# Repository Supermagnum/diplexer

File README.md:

# diplexer
HF+6M lowpass and 4M highpass

The lowpass filter has: 71.5mhz -42dB. 
Highpass filter 52.5mhz -45dB. 50.5mhz -50db

Highpass Ltspice analysis setup:

Highpass frequency analysis ( insertion loss, insertion phase, and return loss):

Highpass Z-in and Z out analysis:

Lowpass LTspice analysis setup:

Lowpass filter frequency analysis ( insertion loss, insertion phase, and return loss):

Lowpass filter Z-in and Z out:

PCB board screenshot:

I had to draw the 1111 SMD footprint because it wasn't included in the Kicad database.
I hope that I haven't messed up.
Shematic for the diplexer:
https://raw.githubusercontent.com/Supermagnum/diplexer/refs/heads/main/diplexer.pdf

Inductors:
You have to make these yourself!
https://github.com/Supermagnum/diplexer/blob/main/Inductors.pdf

Suitable box:
https://www.hammfg.com/part/1457N1601E

All bolt holes is M3.

Animation of assembled PCB:
https://youtu.be/Ffxkk6wFYqY

PCB boards and assembly:

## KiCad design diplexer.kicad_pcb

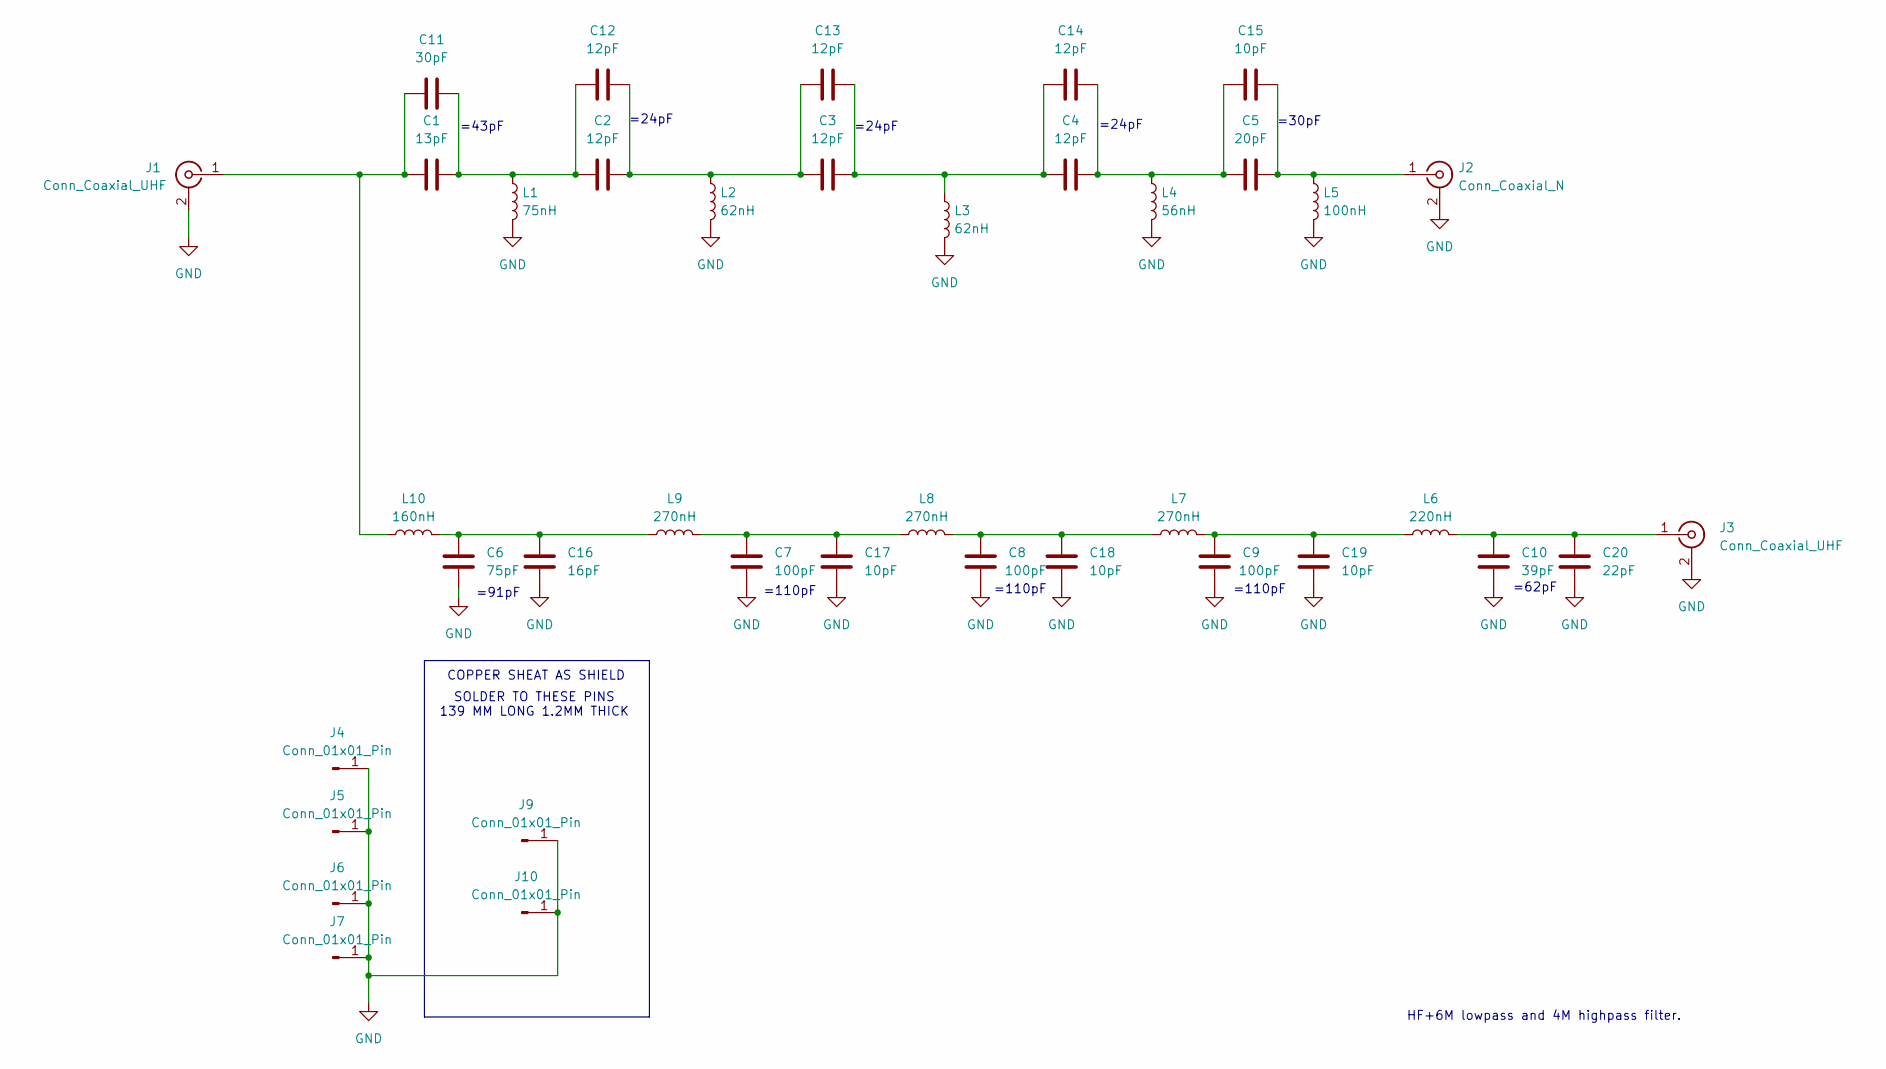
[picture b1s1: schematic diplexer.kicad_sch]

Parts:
C1: 13pF; CAPC2927X178N; MPN VJ1111D130JXGAJ
C2, C3, C4, C12, C13, C14: 12pF; CAPC2927X178N; MPN VJ1111D120GXGQJ
C5: 20pF; CAPC2927X178N; MPN VJ1111D200JXRAJ
C6: 75pF; CAPC2927X178N; MPN VJ1111D750JXGAJ
C7, C8, C9: 100pF; CAPC2927X178N; MPN VJ1111D101GXGQT
C10: 39pF; CAPC2927X178N; MPN VJ1111D390JXRAJ
C11: 30pF; CAPC2927X178N; MPN VJ1111D300GXGQT
C15, C17, C18, C19: 10pF; CAPC2927X178N; MPN VJ1111D100JXRAJ
C16: 16pF; CAPC2927X178N; MPN VJ1111D160GXGQT
C20: 22pF; CAPC2927X178N; MPN VJ1111D220JXRAJ
J1: Conn_Coaxial_UHF; UHF-slant-corr; MPN 083-1R (SO-239)
J2: Conn_Coaxial_N; Conn-N-slant-C; MPN 172117
J3: Conn_Coaxial_UHF; UHF-slant-corr; MPN 83-1R (SO-239)
J4, J5, J6, J7, J9, J10: Conn_01x01_Pin; MountingHole_3.2mm_M3_DIN965_Pad
L1: 75nH; L_Axial_L14.6-hand
L2, L3: 62nH; L_Axial_L14.6-hand
L4: 56nH; L_Axial_L14.6-hand
L5: 100nH; L_Axial_L14.6-hand
L6: 220nH; L_Axial_L14.6-hand
L7, L8, L9: 270nH; L_Axial_L14.6-hand
L10: 160nH; L_Axial_L14.6-hand

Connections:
GND: C6.1, C7.1, C8.1, C9.1, C10.1, C16.2, C17.2, C18.2, C19.2, C20.2, J1.2 (Ext), J1.3, J2.2 (Ext), J2.3, J3.2 (Ext), J3.3, J4.1, J5.1, J6.1, J7.1, J9.1, J10.1, L1.2, L2.2, L3.2, L4.2, L5.2
unnamed: C1.2, C2.1, C11.2, C12.1, L1.1
unnamed: C2.2, C3.1, C12.2, C13.1, L2.1
unnamed: C3.2, C4.1, C13.2, C14.1, L3.1
unnamed: C4.2, C5.1, C14.2, C15.1, L4.1
unnamed: C6.2, C16.1, L9.1, L10.2
unnamed: C7.2, C17.1, L8.1, L9.2
unnamed: C8.2, C18.1, L7.1, L8.2
unnamed: C9.2, C19.1, L6.1, L7.2
unnamed: C1.1, C11.1, J1.1 (In), L10.1
unnamed: C5.2, C15.2, J2.1 (In), L5.1
unnamed: C10.2, C20.1, J3.1 (In), L6.2

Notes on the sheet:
=24pF
=110pF
=43pF
=91pF
=62pF
COPPER SHEAT AS SHIELD
SOLDER TO THESE PINS 139 MM LONG 1.2MM THICK
HF+6M lowpass and 4M highpass filter.
=30pF

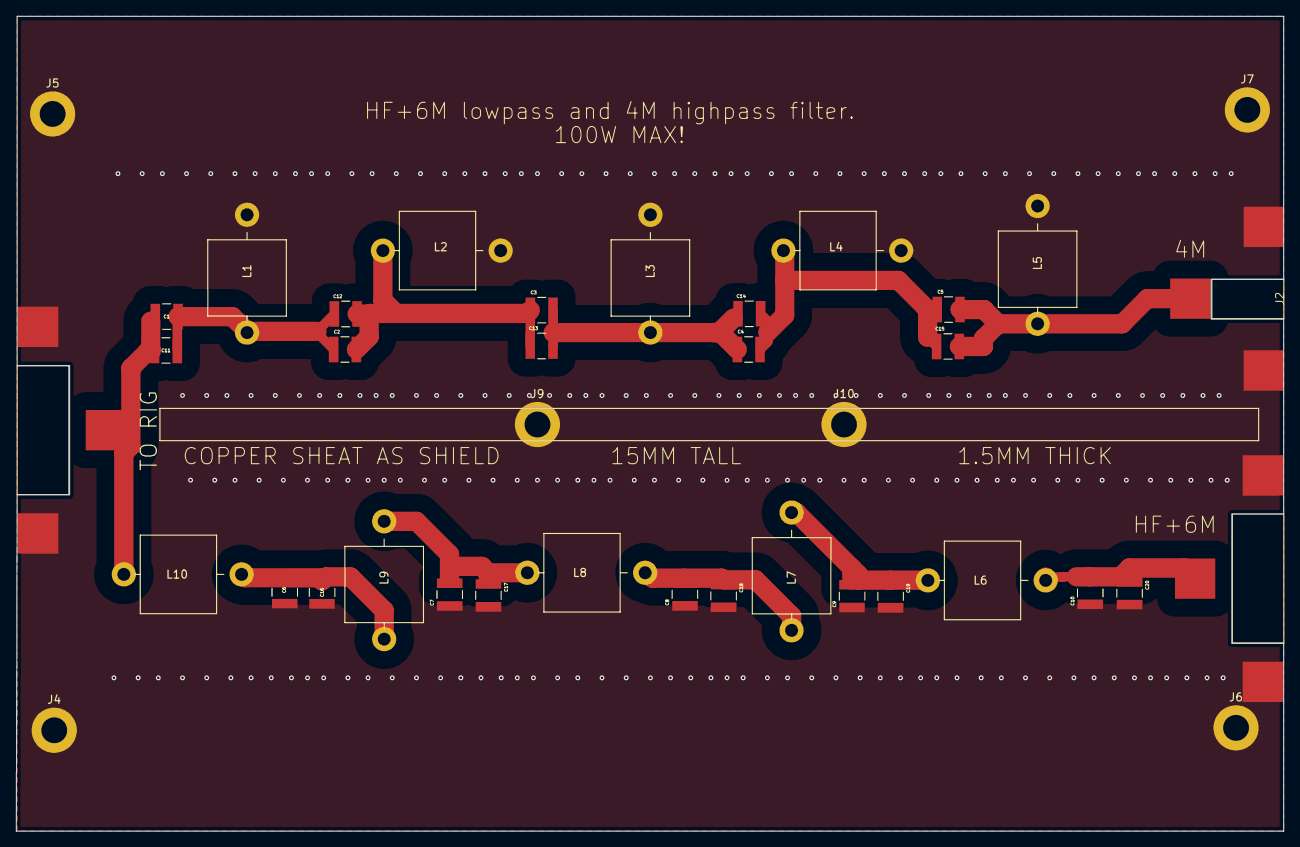
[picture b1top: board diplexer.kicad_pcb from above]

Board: 2 copper layers, 157.1 x 101.0 mm, 39 parts (0 on the bottom side), 12 nets.

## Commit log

2024-03-12 Update README.md
    Added schema diagram
2024-03-12 Inductors
2024-10-11 Add files via upload
    Added gerber and kicad files.
2024-10-12 Add files via upload
    Updated capacitors foot prints to 2525 (QEEV Series)
2024-10-13 Delete Gerbers/Gerbers.zip
    outdated
2024-11-29 Add files via upload
    Added cutouts for connectors
2024-11-29 Add files via upload
    fixed old pictures
